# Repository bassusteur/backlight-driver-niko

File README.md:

# Niko backlight driver
This is a **backlight driver** module for [project Koyomi - HDMI to LVDS adapter](https://github.com/exentio/koyomi-hdmi-lvds)  
I called it [Niko](https://store.steampowered.com/app/420530/OneShot/)!

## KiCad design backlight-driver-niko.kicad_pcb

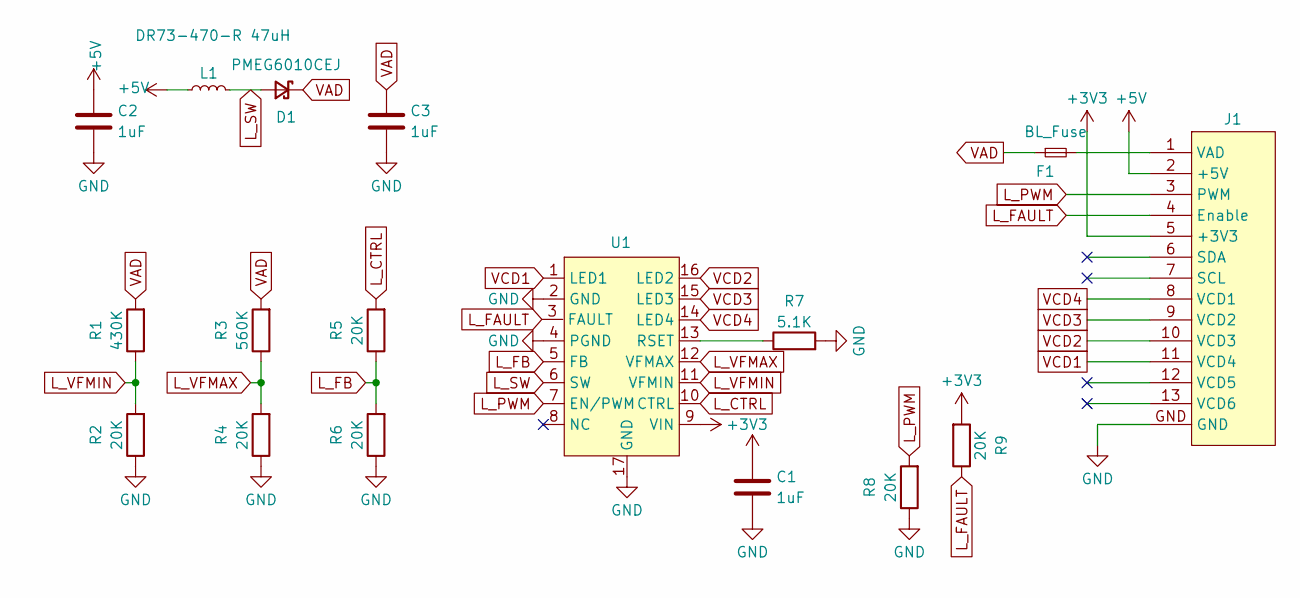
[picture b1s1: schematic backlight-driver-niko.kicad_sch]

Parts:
C1: 1uF; C_0402_1005Metric
C2, C3: 1uF; C_0805_2012Metric
D1: PMEG6010CEJ; D_SOD-323F
F1: BL_Fuse; Fuse_0805_2012Metric
J1: koyomi_bl_test_driver
L1: DR73-470-R 47uH; L_Coilcraft_XAL6020-XXX
R1: 430K; R_0402_1005Metric
R2, R4, R5, R6, R8, R9: 20K; R_0402_1005Metric
R3: 560K; R_0402_1005Metric
R7: 5.1K; R_0402_1005Metric
U1: TQFN-16-1EP_3x3mm_P0.5mm_EP1.23x1.23mm

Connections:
+3V3: C1.1, J1.5 (+3V3), R9.2, U1.9 (VIN)
+5V: C2.1, J1.2 (+5V), L1.1
GND: C1.2, C2.2, C3.2, J1.GND, R2.1, R4.1, R6.1, R7.2, R8.1, U1.2 (GND), U1.4 (PGND), U1.17 (GND)
L_CTRL: R5.2, U1.10 (CTRL)
L_FAULT: J1.4 (Enable), R9.1, U1.3 (FAULT)
L_FB: R5.1, R6.2, U1.5 (FB)
L_PWM: J1.3 (PWM), R8.2, U1.7 (EN/PWM)
L_SW: D1.2 (A), L1.2, U1.6 (SW)
L_VFMAX: R3.1, R4.2, U1.12 (VFMAX)
L_VFMIN: R1.1, R2.2, U1.11 (VFMIN)
unnamed: F1.2, J1.1 (VAD)
unnamed: R7.1, U1.13 (RSET)
VAD: C3.1, D1.1 (K), F1.1, R1.2, R3.2
VCD1: J1.11 (VCD4), U1.1 (LED1)
VCD2: J1.10 (VCD3), U1.16 (LED2)
VCD3: J1.9 (VCD2), U1.15 (LED3)
VCD4: J1.8 (VCD1), U1.14 (LED4)

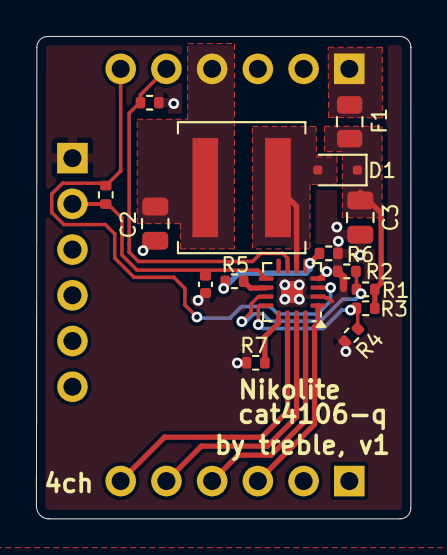
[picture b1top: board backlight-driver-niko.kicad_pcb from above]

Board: 2 copper layers, 20.8 x 26.8 mm, 17 parts (0 on the bottom side), 17 nets.

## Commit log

2024-10-26 Nikolite reviewed, silkscreen improved, added fuse, fixed a few small things wrt layout/sch
